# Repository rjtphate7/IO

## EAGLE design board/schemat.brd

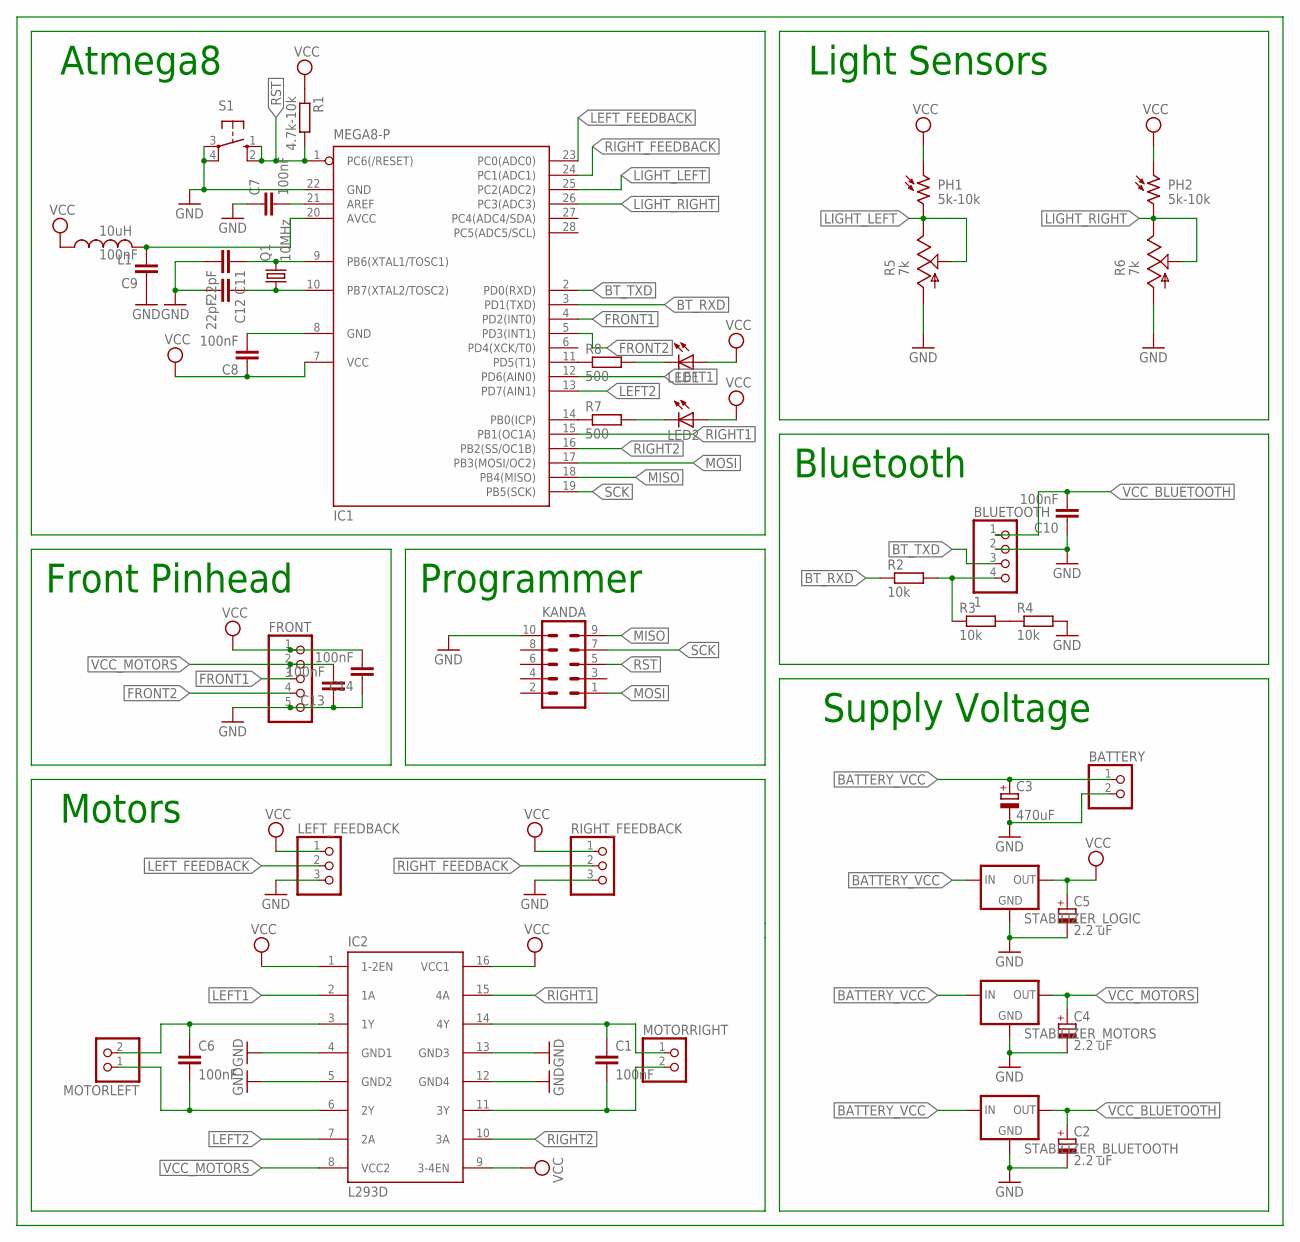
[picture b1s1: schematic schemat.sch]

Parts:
BATTERY: PINHD-1X2; 1X02
BLUETOOTH: 1; 1X04
C1, C6, C7, C8, C9, C10, C13, C14: 100nF; C2.5-3
C2, C4, C5: 2.2 uF; E1,8-4
C3: 470uF; E3,5-8
C11, C12: 22pF; C2.5-3
FRONT: PINHD-1X5; 1X05
IC1: MEGA8-P; DIL28-3
IC2: L293D; DIL16
KANDA: ML10
L1: 10uH; 0204/7
LED1, LED2: LEDSFH480; SFH480
LEFT_FEEDBACK: PINHD-1X3; 1X03
MOTORLEFT: PINHD-1X2; 1X02
MOTORRIGHT: PINHD-1X2; 1X02
PH1, PH2: 5k-10k; VT800
Q1: 10MHz; HC49U-V
R1: 4.7k-10k; 0204/7
R2, R3, R4: 10k; 0204/7
R5, R6: 7k; CA6V
R7, R8: 500; 0204/7
RIGHT_FEEDBACK: PINHD-1X3; 1X03
S1: 10-XX; B3F-10XX
STABILIZER_BLUETOOTH: 78XXS
STABILIZER_LOGIC: 78XXS
STABILIZER_MOTORS: 78XXS

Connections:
BATTERY_VCC: BATTERY.1, C3.+, STABILIZER_BLUETOOTH.IN, STABILIZER_LOGIC.IN, STABILIZER_MOTORS.IN
BT_RXD: IC1.3 (PD1(TXD)), R2.1
BT_TXD: BLUETOOTH.3, IC1.2 (PD0(RXD))
FRONT1: FRONT.3, IC1.4 (PD2(INT0))
FRONT2: FRONT.4, IC1.5 (PD3(INT1))
GND: BATTERY.2, BLUETOOTH.2, C2.-, C3.-, C4.-, C5.-, C7.1, C9.1, C10.1, C11.2, C12.2, C13.1, C14.1, FRONT.5, IC1.22 (GND), IC2.4 (GND1), IC2.5 (GND2), IC2.12 (GND4), IC2.13 (GND3), KANDA.10, LEFT_FEEDBACK.3, R4.2, R5.A, R6.A, RIGHT_FEEDBACK.3, S1.3, S1.4 (P1), STABILIZER_BLUETOOTH.GND, STABILIZER_LOGIC.GND, STABILIZER_MOTORS.GND
LEFT1: IC1.12 (PD6(AIN0)), IC2.2 (1A)
LEFT2: IC1.13 (PD7(AIN1)), IC2.7 (2A)
LEFT_FEEDBACK: IC1.23 (PC0(ADC0)), LEFT_FEEDBACK.2
LIGHT_LEFT: IC1.25 (PC2(ADC2)), PH1.2, R5.E, R5.S
LIGHT_RIGHT: IC1.26 (PC3(ADC3)), PH2.2, R6.E, R6.S
MISO: IC1.18 (PB4(MISO)), KANDA.9
MOSI: IC1.17 (PB3(MOSI/OC2)), KANDA.1
unnamed: C7.2, IC1.21 (AREF)
unnamed: C6.1, IC2.3 (1Y), MOTORLEFT.2
unnamed: C6.2, IC2.6 (2Y), MOTORLEFT.1
unnamed: C1.1, IC2.14 (4Y), MOTORRIGHT.1
unnamed: C1.2, IC2.11 (3Y), MOTORRIGHT.2
unnamed: C9.2, IC1.20 (AVCC), L1.2
unnamed: C8.2, IC1.8 (GND)
unnamed: R3.2, R4.1
unnamed: BLUETOOTH.4, R2.2, R3.1
unnamed: C12.1, IC1.10 (PB7(XTAL2/TOSC2)), Q1.1
unnamed: C11.1, IC1.9 (PB6(XTAL1/TOSC1)), Q1.2
unnamed: IC1.14 (PB0(ICP)), R7.1
unnamed: IC1.11 (PD5(T1)), R8.1
unnamed: LED2.K (C), R7.2
unnamed: LED1.K (C), R8.2
RIGHT1: IC1.15 (PB1(OC1A)), IC2.15 (4A)
RIGHT2: IC1.16 (PB2(SS/OC1B)), IC2.10 (3A)
RIGHT_FEEDBACK: IC1.24 (PC1(ADC1)), RIGHT_FEEDBACK.2
RST: IC1.1 (PC6(/RESET)), KANDA.5, R1.2, S1.1 (S), S1.2 (S1)
SCK: IC1.19 (PB5(SCK)), KANDA.7
VCC: C5.+, C8.1, C14.2, FRONT.1, IC1.7 (VCC), IC2.1 (1-2EN), IC2.9 (3-4EN), IC2.16 (VCC1), L1.1, LED1.A, LED2.A, LEFT_FEEDBACK.1, PH1.1, PH2.1, R1.1, RIGHT_FEEDBACK.1, STABILIZER_LOGIC.OUT
VCC_BLUETOOTH: BLUETOOTH.1, C2.+, C10.2, STABILIZER_BLUETOOTH.OUT
VCC_MOTORS: C4.+, C13.2, FRONT.2, IC2.8 (VCC2), STABILIZER_MOTORS.OUT

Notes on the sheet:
Motors
Front Pinhead
Programmer
Supply Voltage
Bluetooth
Atmega8
Light Sensors

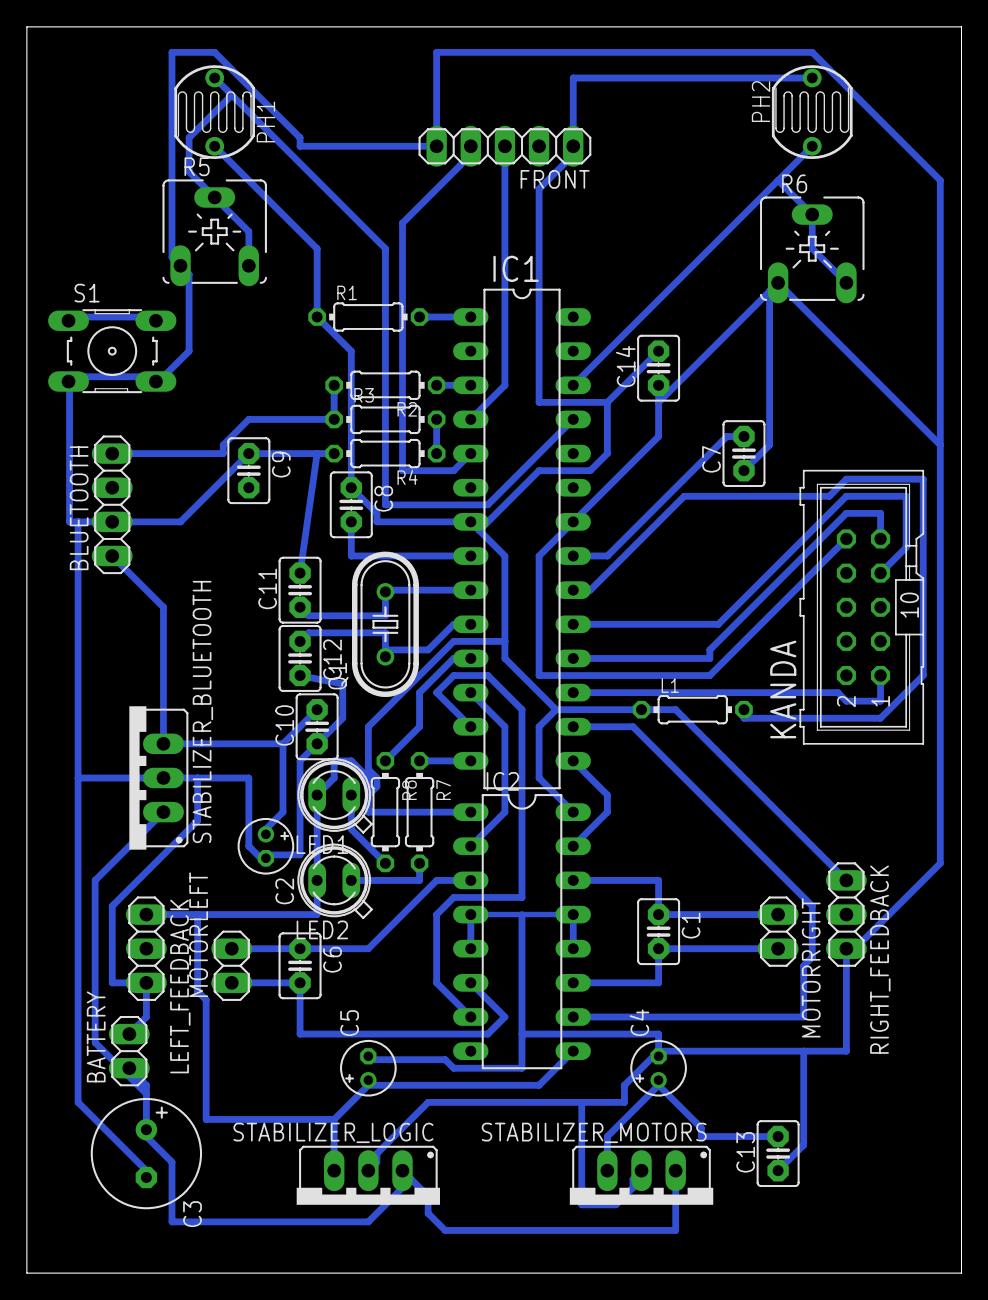
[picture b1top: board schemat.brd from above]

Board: 2 copper layers, 69.5 x 92.7 mm, 42 parts (0 on the bottom side), 36 nets.

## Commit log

2018-04-12 Adding on github
2018-04-12 Updeted gitignore a bit
2018-04-19 Fixed position of few capasitors
